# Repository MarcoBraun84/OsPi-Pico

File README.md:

Hier sind alle Projektdatein zum Projekt "OsPi Pico" aus Embedded Systems I vom WS23/24 zu finden.\
Teils wird in "final" und "V1" unterschieden, final bedeutet den Stand am Ende des Projektes, V1 bezieht sich auf die physisch existierenden Platinen.
Sollte an diesen etwas gesucht/geändert werden, kann man sich auzf diese Datein beziehen. Jegliche Verbesserungen oder Weiterentwicklungen sollten aber an den "final" Datein getätigt werden. \

Das Projekt wurde mit Fusion 360 druchgeführt, daher sind viele der umfangreicheren Datein zur Platine nur damit zu öffnen.

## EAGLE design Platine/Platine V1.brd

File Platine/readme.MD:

Die Platinen wurden bei [JLCPCB](https://jlcpcb.com/) gefertigt, ein passender Design-Regelsatz für Fusion 360 kann [hier](https://github.com/oxullo/jlcpcb-eagle) gefunden werden.

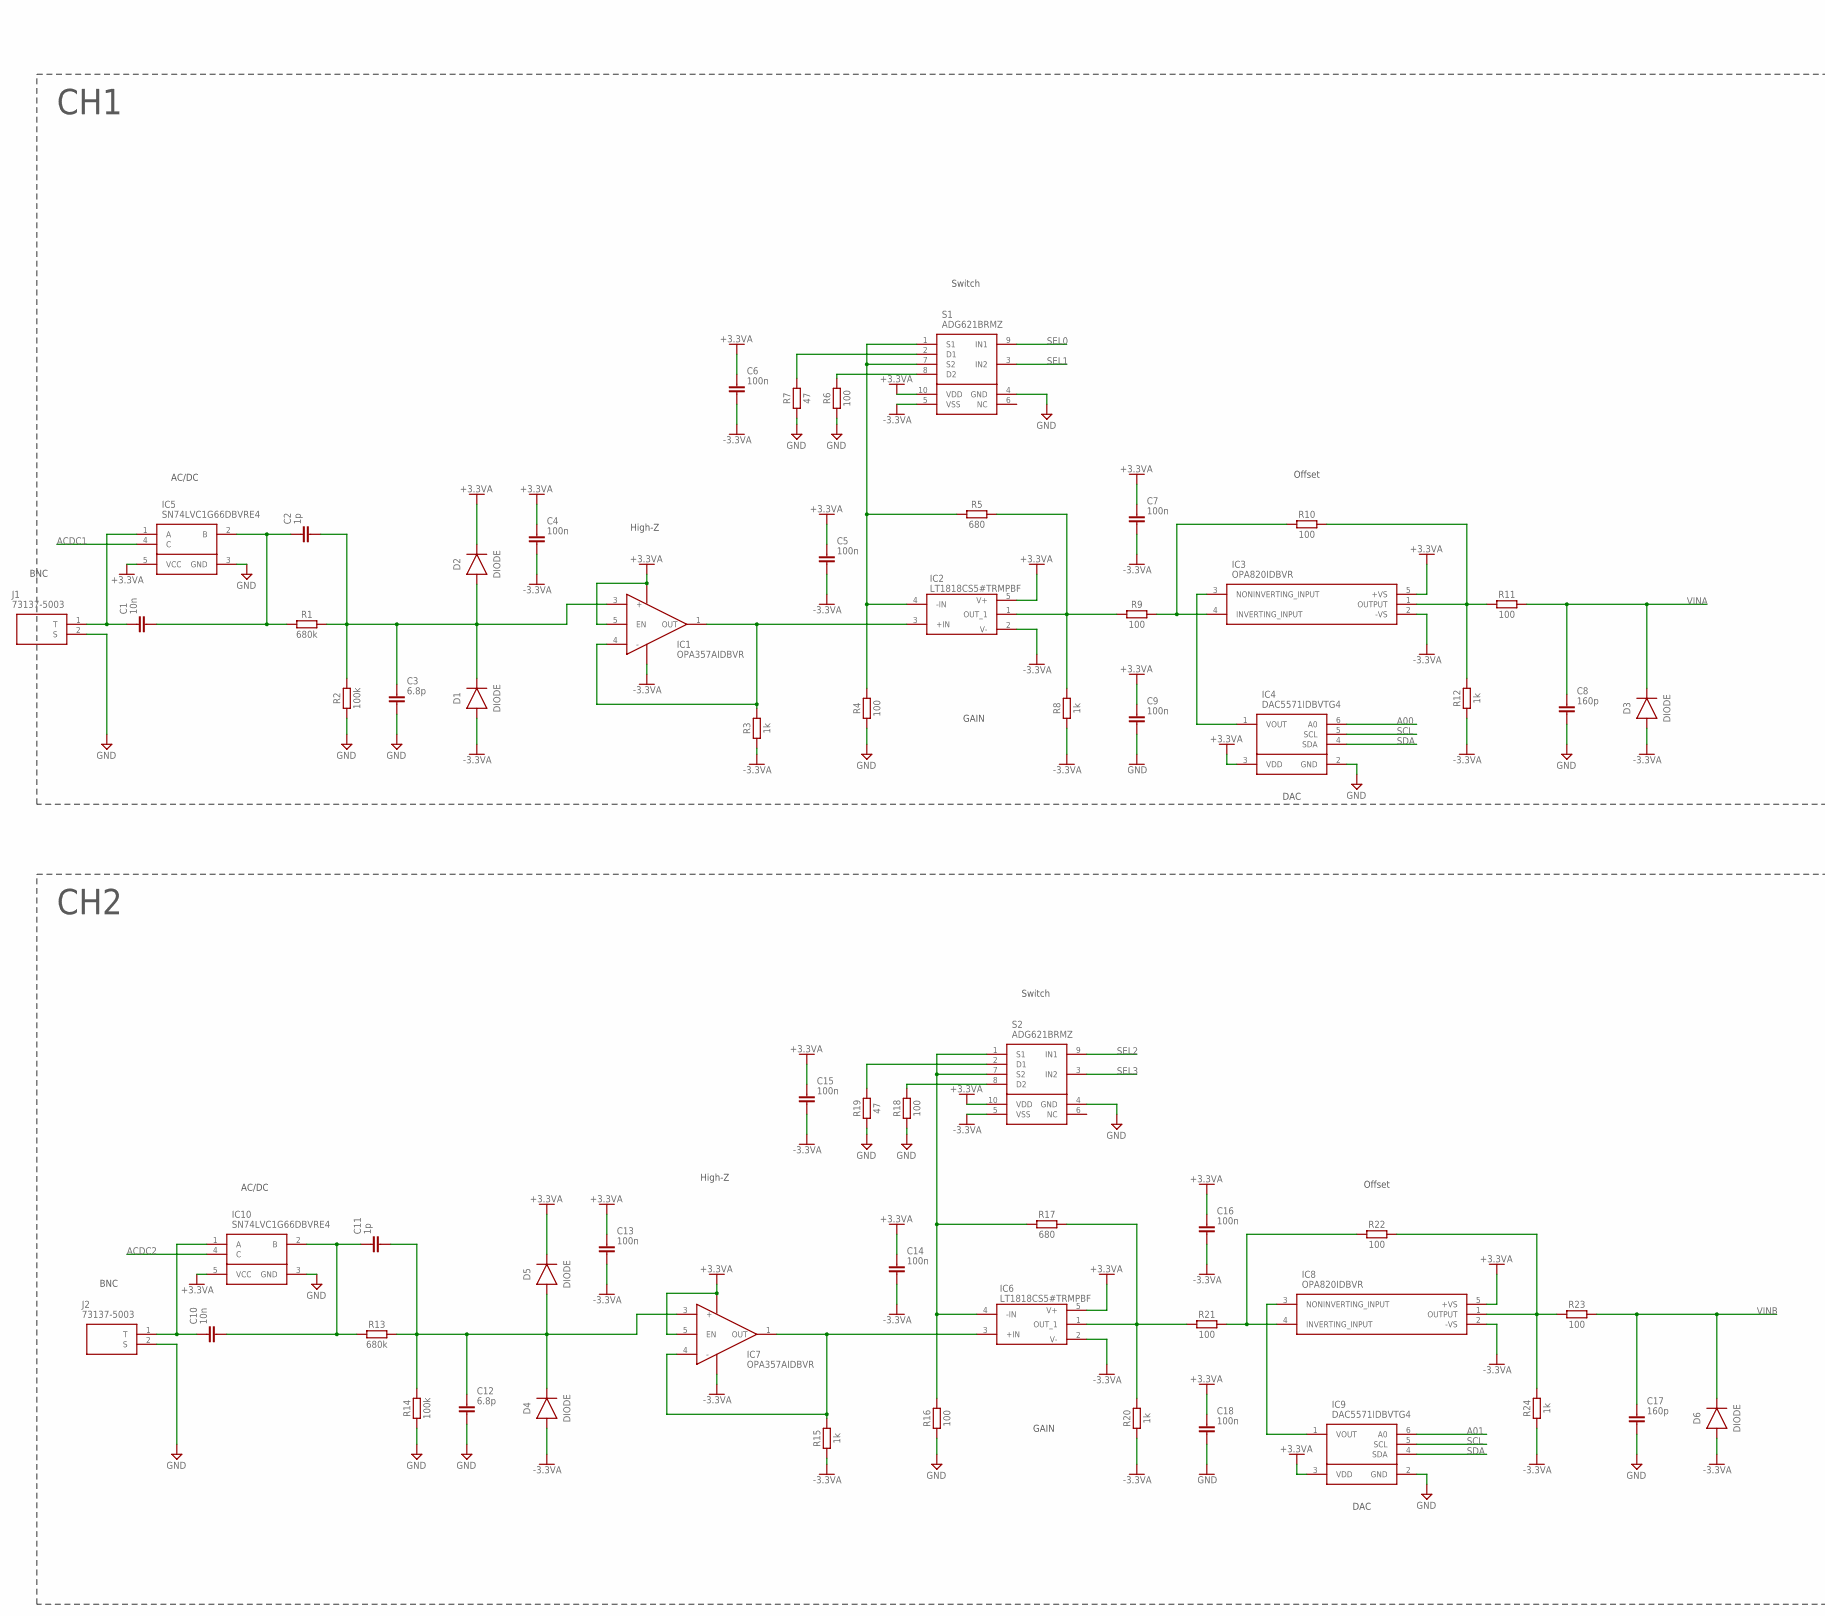
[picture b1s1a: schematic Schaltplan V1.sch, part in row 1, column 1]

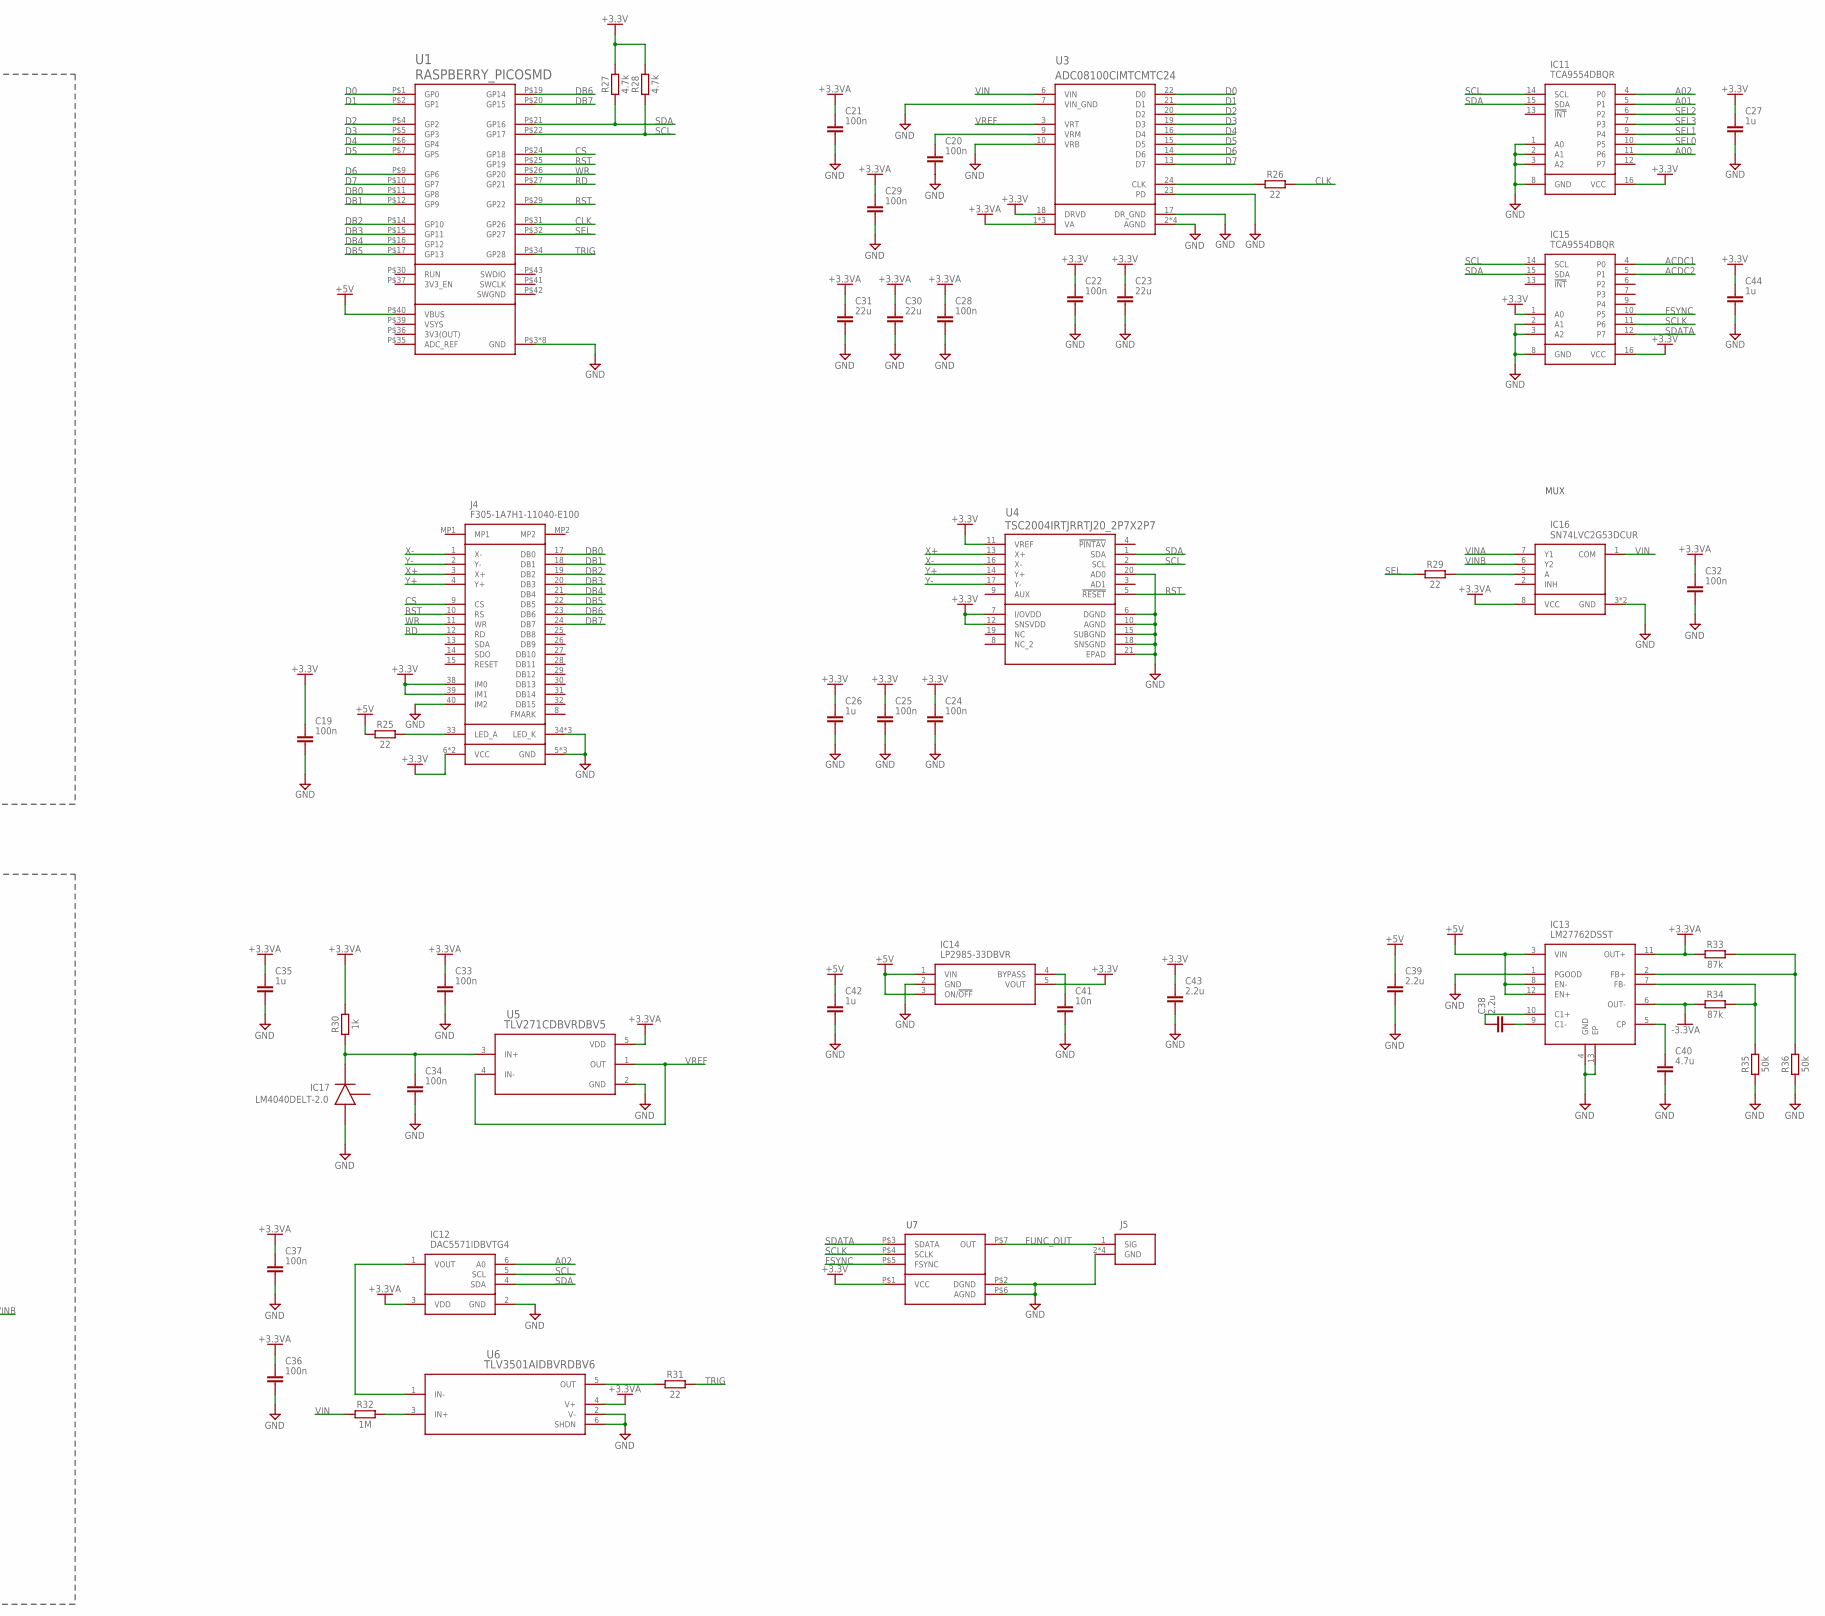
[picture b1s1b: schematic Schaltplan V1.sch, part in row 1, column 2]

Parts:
C1, C10, C41: 10n; CAPC2012X110
C2, C11: 1p; CAPC2012X110
C3, C12: 6.8p; CAPC2012X110
C4, C5, C6, C7, C9, C13, C14, C15, C16, C18, C19, C20, C21, C22, C24, C25, C28, C29, C32, C33, C34, C36, C37: 100n; CAPC2012X110
C8, C17: 160p; CAPC2012X110
C23, C30, C31: 22u; CAPC2012X110
C26, C27, C35, C42, C44: 1u; CAPC2012X110
C38, C39, C43: 2.2u; CAPC2012X110
C40: 4.7u; CAPC2012X110
D1, D2, D3, D4, D5, D6: DIODE; SODFL2513X70
IC1, IC7: OPA357AIDBVR; SOT95P280X145-6N
IC2, IC6: LT1818CS5#TRMPBF; SOT95P280X100-5N
IC3, IC8: OPA820IDBVR; SOT95P280X145-5N
IC4, IC9, IC12: DAC5571IDBVTG4; SOT95P280X145-6N
IC5, IC10: SN74LVC1G66DBVRE4; SOT95P280X145-5N
IC11, IC15: TCA9554DBQR; SOP64P600X175-16N
IC13: LM27762DSST; SON50P200X300X80-13N
IC14: LP2985-33DBVR; SOT95P280X145-5N
IC16: SN74LVC2G53DCUR; SOP50P310X90-8N
IC17: LM4040DELT-2.0; SOT65P210X110-3N
J1, J2: 73137-5003; 731375003
J4: F305-1A7H1-11040-E100; F3051A7H111040E100
J5: PCB.SMAFRA.HT; PCBSMAFRAHT
R1, R13: 680k; RESC2012X65
R2, R14: 100k; RESC2012X65
R3, R8, R12, R15, R20, R24, R30: 1k; RESC2012X65
R4, R6, R9, R10, R11, R16, R18, R21, R22, R23: 100; RESC2012X65
R5, R17: 680; RESC2012X65
R7, R19: 47; RESC2012X65
R25, R26, R29, R31: 22; RESC2012X65
R27, R28: 4.7k; RESC2012X65
R32: 1M; RESC2012X65
R33, R34: 87k; RESC2012X65
R35, R36: 50k; RESC2012X65
S1, S2: ADG621BRMZ; SOP50P490X110-10N
U1: RASPBERRY_PICOSMD; PICO-PKG-SMD
U3: ADC08100CIMTCMTC24; MTC24
U4: TSC2004IRTJRRTJ20_2P7X2P7; RTJ20_2P7X2P7
U5: TLV271CDBVRDBV5; DBV5
U6: TLV3501AIDBVRDBV6; DBV6
U7: AD9833FUNCGEN

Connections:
3V3(OUT): U1.P$36 (3V3(OUT))
+3.3V: C19.1, C22.1, C23.1, C24.1, C25.1, C26.1, C27.1, C43.1, C44.1, IC11.16 (VCC), IC14.5 (VOUT), IC15.1 (A0), IC15.16 (VCC), J4.6 (VCC), J4.7 (VCC), J4.38 (IM0), J4.39 (IM1), R27.2, R28.2, U3.18 (DRVD), U4.7 (I/OVDD), U4.11 (VREF), U4.12 (SNSVDD), U7.P$1 (VCC)
+3.3VA: C4.1, C5.1, C6.1, C7.1, C9.1, C13.1, C14.1, C15.1, C16.1, C18.1, C21.1, C28.1, C29.1, C30.1, C31.1, C32.1, C33.1, C35.1, C36.1, C37.1, D2.1 (C), D5.1 (C), IC1.5 (EN), IC1.6 (V+), IC2.5 (V+), IC3.5 (+VS), IC4.3 (VDD), IC5.5 (VCC), IC6.5 (V+), IC7.5 (EN), IC7.6 (V+), IC8.5 (+VS), IC9.3 (VDD), IC10.5 (VCC), IC12.3 (VDD), IC13.11 (OUT+), IC16.8 (VCC), R30.2, R33.1, S1.10 (VDD), S2.10 (VDD), U3.1 (VA), U3.4 (VA), U3.12 (VA), U5.5 (VDD), U6.4 (V+)
+3.3VA1: C34.1, IC17.1 (K), R30.1, U5.3 (IN+)
+5V: C39.1, C42.1, IC13.3 (VIN), IC13.8 (EN-), IC13.12 (EN+), IC14.1 (VIN), IC14.3 (ON/!OFF), R25.1, U1.P$40 (VBUS)
-3.3VA: C4.2, C5.2, C6.2, C7.2, C13.2, C14.2, C15.2, C16.2, D1.2 (A), D3.2 (A), D4.2 (A), D6.2 (A), IC1.2 (V-), IC2.2 (V-), IC3.2 (-VS), IC6.2 (V-), IC7.2 (V-), IC8.2 (-VS), IC13.6 (OUT-), R3.1, R8.1, R12.1, R15.1, R20.1, R24.1, R34.1, S1.5 (VSS), S2.5 (VSS)
A00: IC4.6 (A0), IC11.11 (P6)
A01: IC9.6 (A0), IC11.5 (P1)
A02: IC11.4 (P0), IC12.6 (A0)
ACDC1: IC5.4 (C), IC15.4 (P0)
ACDC2: IC10.4 (C), IC15.5 (P1)
CLK: R26.2, U1.P$31 (GP26)
CS: J4.9 (CS), U1.P$24 (GP18)
D0: U1.P$1 (GP0), U3.22 (D0)
D1: U1.P$2 (GP1), U3.21 (D1)
D2: U1.P$4 (GP2), U3.20 (D2)
D3: U1.P$5 (GP3), U3.19 (D3)
D4: U1.P$6 (GP4), U3.16 (D4)
D5: U1.P$7 (GP5), U3.15 (D5)
D6: U1.P$9 (GP6), U3.14 (D6)
D7: U1.P$10 (GP7), U3.13 (D7)
DB0: J4.17 (DB0), U1.P$11 (GP8)
DB1: J4.18 (DB1), U1.P$12 (GP9)
DB2: J4.19 (DB2), U1.P$14 (GP10)
DB3: J4.20 (DB3), U1.P$15 (GP11)
DB4: J4.21 (DB4), U1.P$16 (GP12)
DB5: J4.22 (DB5), U1.P$17 (GP13)
DB6: J4.23 (DB6), U1.P$19 (GP14)
DB7: J4.24 (DB7), U1.P$20 (GP15)
FSYNC: IC15.10 (P5), U7.P$5 (FSYNC)
FUNC_OUT: J5.1 (SIG), U7.P$7 (OUT)
GND: C3.2, C8.2, C9.2, C12.2, C17.2, C18.2, C19.2, C20.2, C21.2, C22.2, C23.2, C24.2, C25.2, C26.2, C27.2, C28.2, C29.2, C30.2, C31.2, C32.2, C33.2, C34.2, C35.2, C36.2, C37.2, C39.2, C40.2, C41.2, C42.2, C43.2, C44.2, IC4.2 (GND), IC5.3 (GND), IC9.2 (GND), IC10.3 (GND), IC11.1 (A0), IC11.2 (A1), IC11.3 (A2), IC11.8 (GND), IC12.2 (GND), IC13.1 (PGOOD), IC13.4 (GND), IC13.13 (EP), IC14.2 (GND), IC15.2 (A1), IC15.3 (A2), IC15.8 (GND), IC16.3 (GND), IC16.4 (GND), IC17.2 (A), J1.2 (S), J2.2 (S), J4.5 (GND), J4.16 (GND), J4.34 (LED_K), J4.35 (LED_K), J4.36 (LED_K), J4.37 (GND), J4.40 (IM2), J5.2 (GND), J5.3 (GND), J5.4 (GND), J5.5 (GND), R2.1, R4.1, R6.1, R7.1, R14.1, R16.1, R18.1, R19.1, R35.1, R36.1, S1.4 (GND), S2.4 (GND), U1.P$3 (GND), U1.P$8 (GND), U1.P$13 (GND), U1.P$18 (GND), U1.P$23 (GND), U1.P$28 (GND), U1.P$33 (GND), U1.P$38 (GND), U3.2 (AGND), U3.5 (AGND), U3.7 (VIN_GND), U3.8 (AGND), U3.10 (VRB), U3.11 (AGND), U3.17 (DR_GND), U3.23 (PD), U4.6 (DGND), U4.10 (AGND), U4.15 (SUBGND), U4.18 (SNSGND), U4.20 (AD0), U4.21 (EPAD), U5.2 (GND), U6.2 (V-), U6.6 (SHDN), U7.P$2 (DGND), U7.P$6 (AGND)
unnamed: C1.1, IC5.1 (A), J1.1 (T)
unnamed: C1.2, C2.1, IC5.2 (B), R1.1
unnamed: C2.2, C3.1, D1.1 (C), D2.2 (A), IC1.3 (+), R1.2, R2.2
unnamed: R7.2, S1.2 (D1)
unnamed: IC2.4 (-IN), R4.2, R5.1, S1.1 (S1), S1.7 (S2)
unnamed: IC2.1 (OUT_1), R5.2, R8.2, R9.1
unnamed: IC1.1 (OUT), IC1.4 (-), IC2.3 (+IN), R3.2
unnamed: R6.2, S1.8 (D2)
unnamed: IC3.4 (INVERTING_INPUT), R9.2, R10.1
unnamed: IC3.1 (OUTPUT), R10.2, R11.1, R12.2
unnamed: IC3.3 (NONINVERTING_INPUT), IC4.1 (VOUT)
unnamed: C10.1, IC10.1 (A), J2.1 (T)
unnamed: C10.2, C11.1, IC10.2 (B), R13.1
unnamed: C11.2, C12.1, D4.1 (C), D5.2 (A), IC7.3 (+), R13.2, R14.2
unnamed: IC6.4 (-IN), R16.2, R17.1, S2.1 (S1), S2.7 (S2)
unnamed: IC6.1 (OUT_1), R17.2, R20.2, R21.1
unnamed: IC6.3 (+IN), IC7.1 (OUT), IC7.4 (-), R15.2
unnamed: R19.2, S2.2 (D1)
unnamed: R18.2, S2.8 (D2)
unnamed: IC8.4 (INVERTING_INPUT), R21.2, R22.1
unnamed: IC8.1 (OUTPUT), R22.2, R23.1, R24.2
unnamed: IC8.3 (NONINVERTING_INPUT), IC9.1 (VOUT)
unnamed: R31.1, U6.5 (OUT)
unnamed: R32.2, U6.3 (IN+)
unnamed: IC12.1 (VOUT), U6.1 (IN-)
unnamed: C20.1, U3.9 (VRM)
unnamed: J4.33 (LED_A), R25.2
unnamed: C40.1, IC13.5 (CP)
unnamed: IC13.2 (FB+), R33.2, R36.2
unnamed: C41.1, IC14.4 (BYPASS)
unnamed: IC13.7 (FB-), R34.2, R35.2
unnamed: C38.1, IC13.10 (C1+)
unnamed: C38.2, IC13.9 (C1-)
unnamed: IC16.5 (A), R29.2
unnamed: R26.1, U3.24 (CLK)
RD: J4.12 (RD), U1.P$27 (GP21)
SCL: IC4.5 (SCL), IC9.5 (SCL), IC11.14 (SCL), IC12.5 (SCL), IC15.14 (SCL), R28.1, U1.P$22 (GP17), U4.2 (SCL)
SCLK: IC15.11 (P6), U7.P$4 (SCLK)
SDA: IC4.4 (SDA), IC9.4 (SDA), IC11.15 (SDA), IC12.4 (SDA), IC15.15 (SDA), R27.1, U1.P$21 (GP16), U4.1 (SDA)
SDATA: IC15.12 (P7), U7.P$3 (SDATA)
SEL: R29.1, U1.P$32 (GP27)
SEL0: IC11.10 (P5), S1.9 (IN1)
SEL1: IC11.9 (P4), S1.3 (IN2)
SEL2: IC11.6 (P2), S2.9 (IN1)
SEL3: IC11.7 (P3), S2.3 (IN2)
SWGND: U1.P$42 (SWGND)
TRIG: R31.2, U1.P$34 (GP28)
VIN: IC16.1 (COM), R32.1, U3.6 (VIN)
VINA: C8.1, D3.1 (C), IC16.7 (Y1), R11.2
VINB: C17.1, D6.1 (C), IC16.6 (Y2), R23.2
VREF: U3.3 (VRT), U5.1 (OUT), U5.4 (IN-)
VSYS: U1.P$39 (VSYS)
WR: J4.11 (WR), U1.P$26 (GP20)
X+: J4.3 (X+), U4.13 (X+)
X-: J4.1 (X-), U4.16 (X-)
Y+: J4.4 (Y+), U4.14 (Y+)
Y-: J4.2 (Y-), U4.17 (Y-)

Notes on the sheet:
CH1
BNC
AC/DC
High-Z
Switch
GAIN
Offset
DAC
CH2
MUX

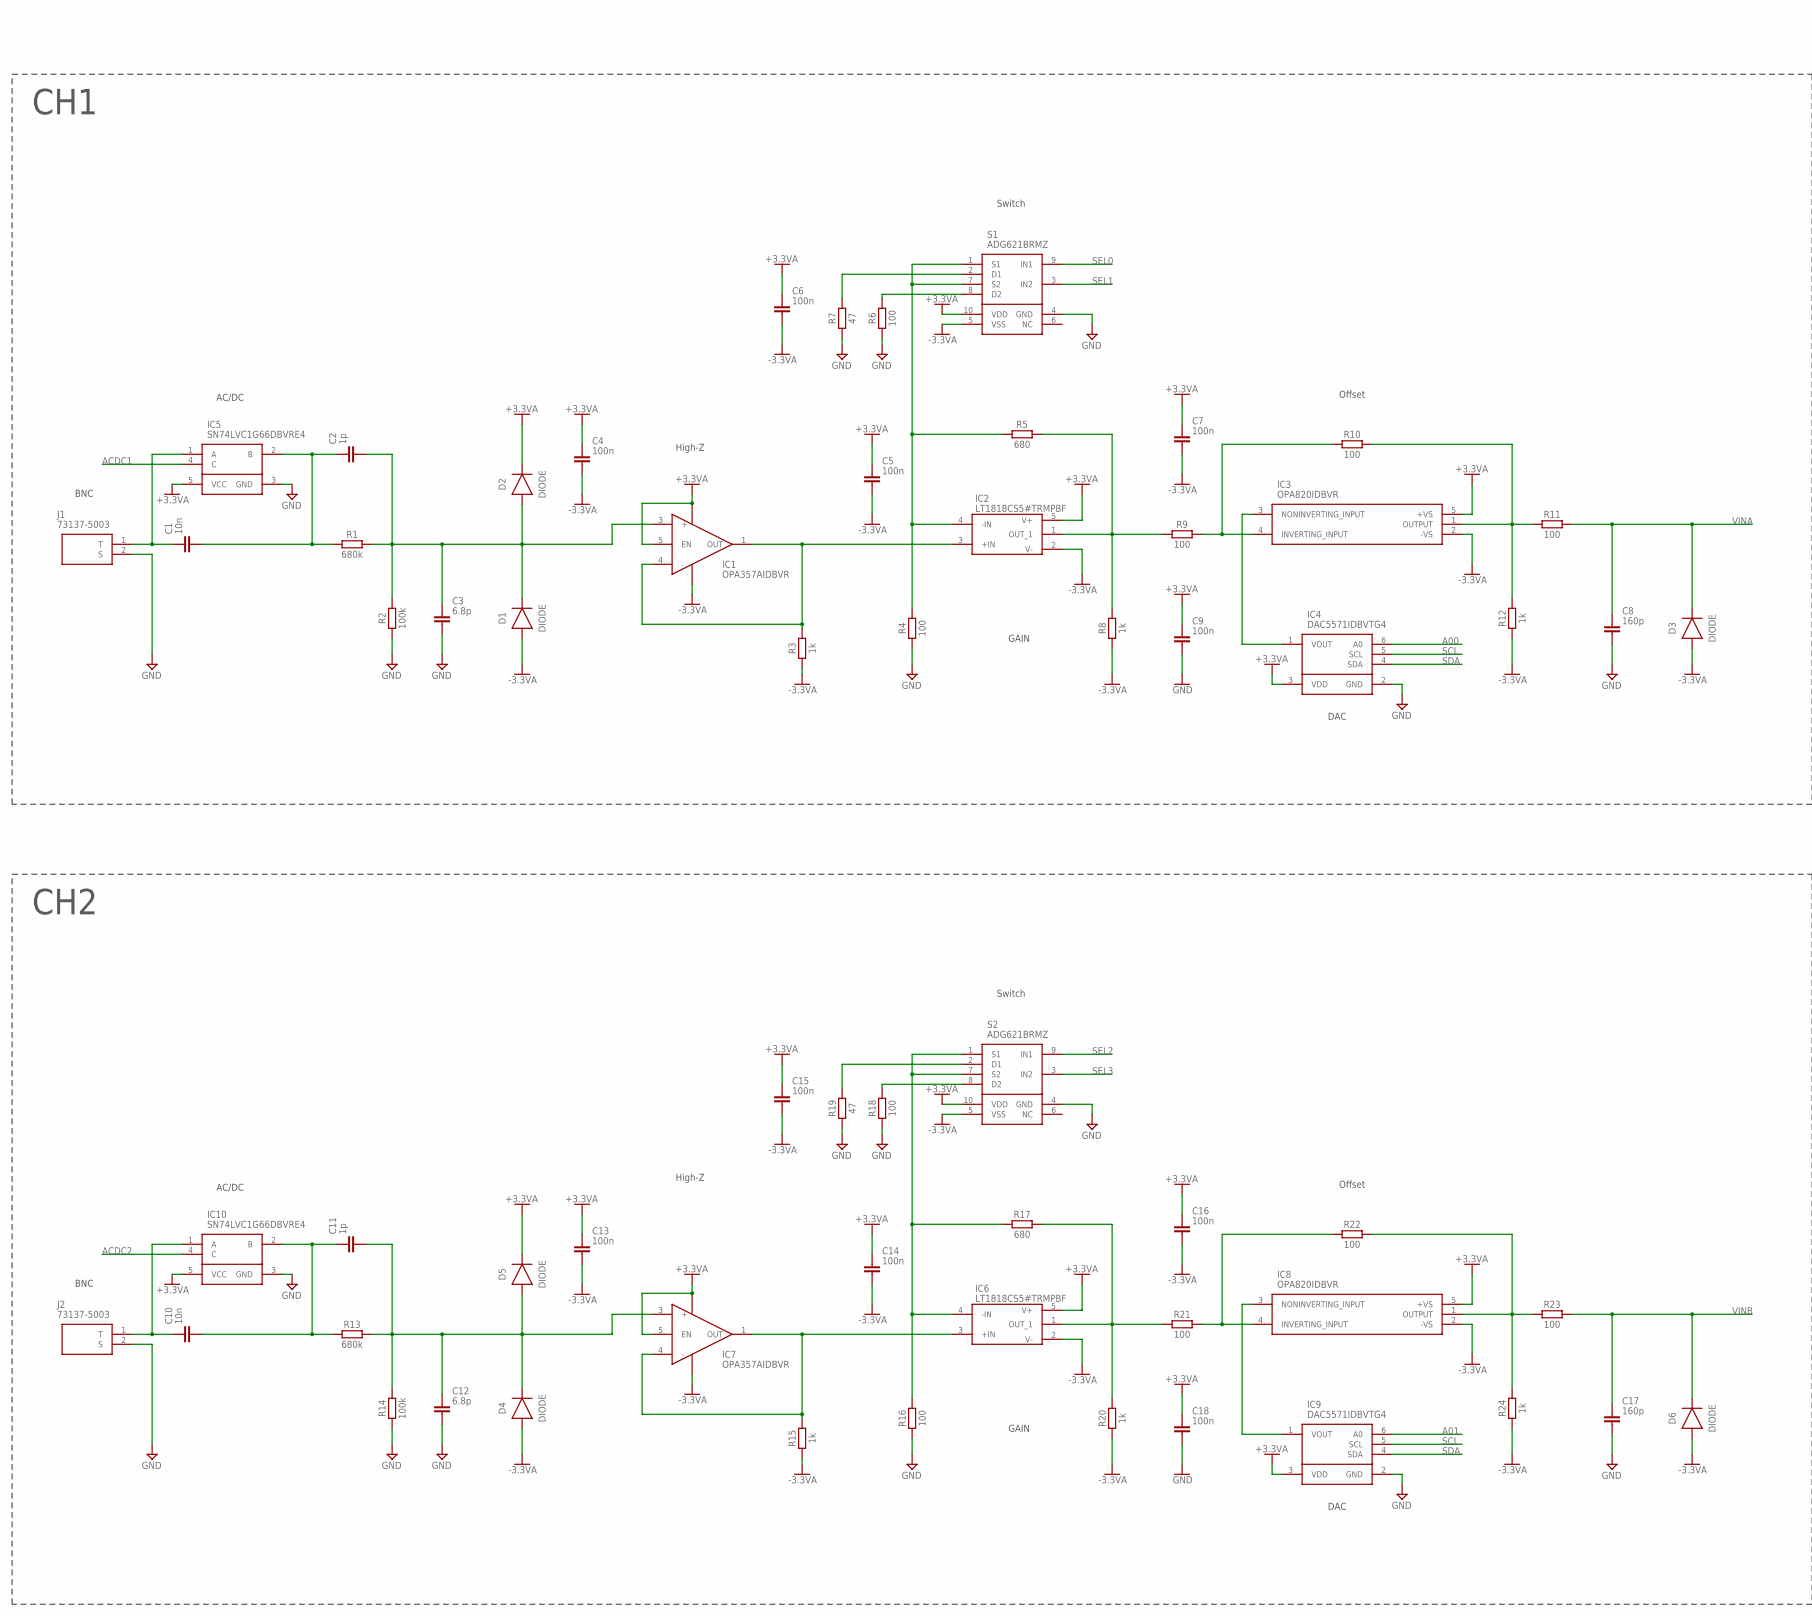
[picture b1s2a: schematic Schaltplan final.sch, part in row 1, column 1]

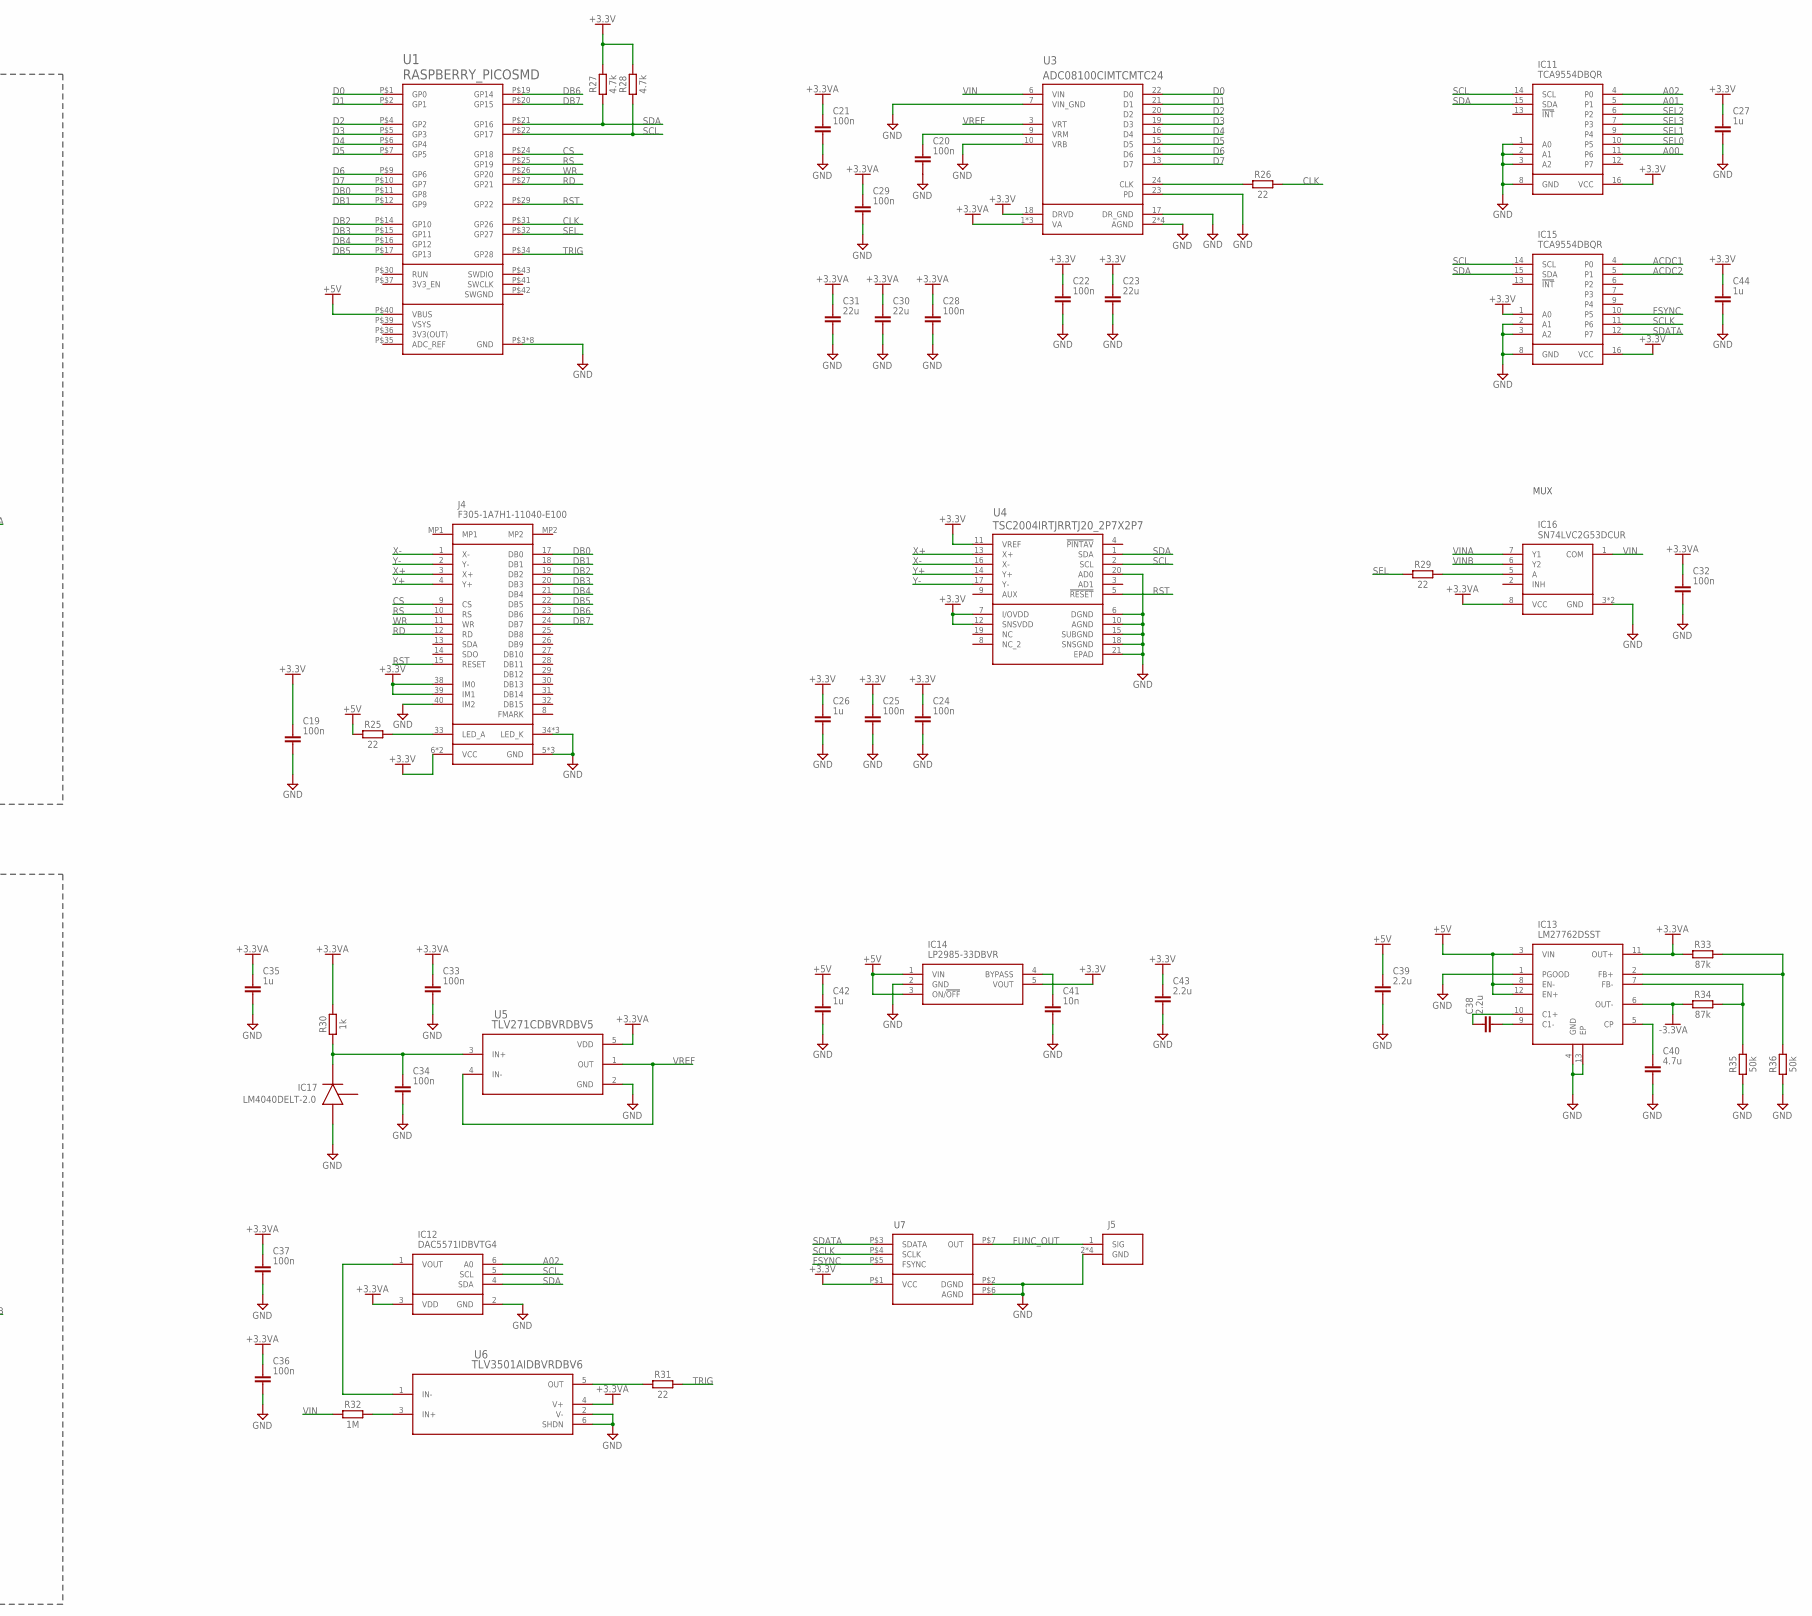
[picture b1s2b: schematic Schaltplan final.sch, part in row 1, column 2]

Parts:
C1, C10, C41: 10n; CAPC2012X110
C2, C11: 1p; CAPC2012X110
C3, C12: 6.8p; CAPC2012X110
C4, C5, C6, C7, C9, C13, C14, C15, C16, C18, C19, C20, C21, C22, C24, C25, C28, C29, C32, C33, C34, C36, C37: 100n; CAPC2012X110
C8, C17: 160p; CAPC2012X110
C23, C30, C31: 22u; CAPC2012X110
C26, C27, C35, C42, C44: 1u; CAPC2012X110
C38, C39, C43: 2.2u; CAPC2012X110
C40: 4.7u; CAPC2012X110
D1, D2, D3, D4, D5, D6: DIODE; SODFL2513X70
IC1, IC7: OPA357AIDBVR; SOT95P280X145-6N
IC2, IC6: LT1818CS5#TRMPBF; SOT95P280X100-5N
IC3, IC8: OPA820IDBVR; SOT95P280X145-5N
IC4, IC9, IC12: DAC5571IDBVTG4; SOT95P280X145-6N
IC5, IC10: SN74LVC1G66DBVRE4; SOT95P280X145-5N
IC11, IC15: TCA9554DBQR; SOP64P600X175-16N
IC13: LM27762DSST; SON50P200X300X80-13N
IC14: LP2985-33DBVR; SOT95P280X145-5N
IC16: SN74LVC2G53DCUR; SOP50P310X90-8N
IC17: LM4040DELT-2.0; SOT65P210X110-3N
J1, J2: 73137-5003; 731375003
J4: F305-1A7H1-11040-E100; F3051A7H111040E100
J5: PCB.SMAFRA.HT; PCBSMAFRAHT
R1, R13: 680k; RESC2012X65
R2, R14: 100k; RESC2012X65
R3, R8, R12, R15, R20, R24, R30: 1k; RESC2012X65
R4, R6, R9, R10, R11, R16, R18, R21, R22, R23: 100; RESC2012X65
R5, R17: 680; RESC2012X65
R7, R19: 47; RESC2012X65
R25, R26, R29, R31: 22; RESC2012X65
R27, R28: 4.7k; RESC2012X65
R32: 1M; RESC2012X65
R33, R34: 87k; RESC2012X65
R35, R36: 50k; RESC2012X65
S1, S2: ADG621BRMZ; SOP50P490X110-10N
U1: RASPBERRY_PICOSMD; PICO-PKG-SMD
U3: ADC08100CIMTCMTC24; MTC24
U4: TSC2004IRTJRRTJ20_2P7X2P7; RTJ20_2P7X2P7
U5: TLV271CDBVRDBV5; DBV5
U6: TLV3501AIDBVRDBV6; DBV6
U7: AD9833FUNCGEN

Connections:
3V3(OUT): U1.P$36 (3V3(OUT))
+3.3V: C19.1, C22.1, C23.1, C24.1, C25.1, C26.1, C27.1, C43.1, C44.1, IC11.16 (VCC), IC14.5 (VOUT), IC15.1 (A0), IC15.16 (VCC), J4.6 (VCC), J4.7 (VCC), J4.38 (IM0), J4.39 (IM1), R27.2, R28.2, U3.18 (DRVD), U4.7 (I/OVDD), U4.11 (VREF), U4.12 (SNSVDD), U7.P$1 (VCC)
+3.3VA: C4.1, C5.1, C6.1, C7.1, C9.1, C13.1, C14.1, C15.1, C16.1, C18.1, C21.1, C28.1, C29.1, C30.1, C31.1, C32.1, C33.1, C35.1, C36.1, C37.1, D2.1 (C), D5.1 (C), IC1.5 (EN), IC1.6 (V+), IC2.5 (V+), IC3.5 (+VS), IC4.3 (VDD), IC5.5 (VCC), IC6.5 (V+), IC7.5 (EN), IC7.6 (V+), IC8.5 (+VS), IC9.3 (VDD), IC10.5 (VCC), IC12.3 (VDD), IC13.11 (OUT+), IC16.8 (VCC), R30.2, R33.1, S1.10 (VDD), S2.10 (VDD), U3.1 (VA), U3.4 (VA), U3.12 (VA), U5.5 (VDD), U6.4 (V+)
+3.3VA1: C34.1, IC17.1 (K), R30.1, U5.3 (IN+)
+5V: C39.1, C42.1, IC13.3 (VIN), IC13.8 (EN-), IC13.12 (EN+), IC14.1 (VIN), IC14.3 (ON/!OFF), R25.1, U1.P$40 (VBUS)
-3.3VA: C4.2, C5.2, C6.2, C7.2, C13.2, C14.2, C15.2, C16.2, D1.2 (A), D3.2 (A), D4.2 (A), D6.2 (A), IC1.2 (V-), IC2.2 (V-), IC3.2 (-VS), IC6.2 (V-), IC7.2 (V-), IC8.2 (-VS), IC13.6 (OUT-), R3.1, R8.1, R12.1, R15.1, R20.1, R24.1, R34.1, S1.5 (VSS), S2.5 (VSS)
A00: IC4.6 (A0), IC11.11 (P6)
A01: IC9.6 (A0), IC11.5 (P1)
A02: IC11.4 (P0), IC12.6 (A0)
ACDC1: IC5.4 (C), IC15.4 (P0)
ACDC2: IC10.4 (C), IC15.5 (P1)
CLK: R26.2, U1.P$31 (GP26)
CS: J4.9 (CS), U1.P$24 (GP18)
D0: U1.P$1 (GP0), U3.22 (D0)
D1: U1.P$2 (GP1), U3.21 (D1)
D2: U1.P$4 (GP2), U3.20 (D2)
D3: U1.P$5 (GP3), U3.19 (D3)
D4: U1.P$6 (GP4), U3.16 (D4)
D5: U1.P$7 (GP5), U3.15 (D5)
D6: U1.P$9 (GP6), U3.14 (D6)
D7: U1.P$10 (GP7), U3.13 (D7)
DB0: J4.17 (DB0), U1.P$11 (GP8)
DB1: J4.18 (DB1), U1.P$12 (GP9)
DB2: J4.19 (DB2), U1.P$14 (GP10)
DB3: J4.20 (DB3), U1.P$15 (GP11)
DB4: J4.21 (DB4), U1.P$16 (GP12)
DB5: J4.22 (DB5), U1.P$17 (GP13)
DB6: J4.23 (DB6), U1.P$19 (GP14)
DB7: J4.24 (DB7), U1.P$20 (GP15)
FSYNC: IC15.10 (P5), U7.P$5 (FSYNC)
FUNC_OUT: J5.1 (SIG), U7.P$7 (OUT)
GND: C3.2, C8.2, C9.2, C12.2, C17.2, C18.2, C19.2, C20.2, C21.2, C22.2, C23.2, C24.2, C25.2, C26.2, C27.2, C28.2, C29.2, C30.2, C31.2, C32.2, C33.2, C34.2, C35.2, C36.2, C37.2, C39.2, C40.2, C41.2, C42.2, C43.2, C44.2, IC4.2 (GND), IC5.3 (GND), IC9.2 (GND), IC10.3 (GND), IC11.1 (A0), IC11.2 (A1), IC11.3 (A2), IC11.8 (GND), IC12.2 (GND), IC13.1 (PGOOD), IC13.4 (GND), IC13.13 (EP), IC14.2 (GND), IC15.2 (A1), IC15.3 (A2), IC15.8 (GND), IC16.3 (GND), IC16.4 (GND), IC17.2 (A), J1.2 (S), J2.2 (S), J4.5 (GND), J4.16 (GND), J4.34 (LED_K), J4.35 (LED_K), J4.36 (LED_K), J4.37 (GND), J4.40 (IM2), J5.2 (GND), J5.3 (GND), J5.4 (GND), J5.5 (GND), R2.1, R4.1, R6.1, R7.1, R14.1, R16.1, R18.1, R19.1, R35.1, R36.1, S1.4 (GND), S2.4 (GND), U1.P$3 (GND), U1.P$8 (GND), U1.P$13 (GND), U1.P$18 (GND), U1.P$23 (GND), U1.P$28 (GND), U1.P$33 (GND), U1.P$38 (GND), U3.2 (AGND), U3.5 (AGND), U3.7 (VIN_GND), U3.8 (AGND), U3.10 (VRB), U3.11 (AGND), U3.17 (DR_GND), U3.23 (PD), U4.6 (DGND), U4.10 (AGND), U4.15 (SUBGND), U4.18 (SNSGND), U4.20 (AD0), U4.21 (EPAD), U5.2 (GND), U6.2 (V-), U6.6 (SHDN), U7.P$2 (DGND), U7.P$6 (AGND)
unnamed: C1.1, IC5.1 (A), J1.1 (T)
unnamed: C1.2, C2.1, IC5.2 (B), R1.1
unnamed: C2.2, C3.1, D1.1 (C), D2.2 (A), IC1.3 (+), R1.2, R2.2
unnamed: R7.2, S1.2 (D1)
unnamed: IC2.4 (-IN), R4.2, R5.1, S1.1 (S1), S1.7 (S2)
unnamed: IC2.1 (OUT_1), R5.2, R8.2, R9.1
unnamed: IC1.1 (OUT), IC1.4 (-), IC2.3 (+IN), R3.2
unnamed: R6.2, S1.8 (D2)
unnamed: IC3.4 (INVERTING_INPUT), R9.2, R10.1
unnamed: IC3.1 (OUTPUT), R10.2, R11.1, R12.2
unnamed: IC3.3 (NONINVERTING_INPUT), IC4.1 (VOUT)
unnamed: C10.1, IC10.1 (A), J2.1 (T)
unnamed: C10.2, C11.1, IC10.2 (B), R13.1
unnamed: C11.2, C12.1, D4.1 (C), D5.2 (A), IC7.3 (+), R13.2, R14.2
unnamed: IC6.4 (-IN), R16.2, R17.1, S2.1 (S1), S2.7 (S2)
unnamed: IC6.1 (OUT_1), R17.2, R20.2, R21.1
unnamed: IC6.3 (+IN), IC7.1 (OUT), IC7.4 (-), R15.2
unnamed: R19.2, S2.2 (D1)
unnamed: R18.2, S2.8 (D2)
unnamed: IC8.4 (INVERTING_INPUT), R21.2, R22.1
unnamed: IC8.1 (OUTPUT), R22.2, R23.1, R24.2
unnamed: IC8.3 (NONINVERTING_INPUT), IC9.1 (VOUT)
unnamed: R31.1, U6.5 (OUT)
unnamed: R32.2, U6.3 (IN+)
unnamed: IC12.1 (VOUT), U6.1 (IN-)
unnamed: C20.1, U3.9 (VRM)
unnamed: J4.33 (LED_A), R25.2
unnamed: C40.1, IC13.5 (CP)
unnamed: IC13.2 (FB+), R33.2, R36.2
unnamed: C41.1, IC14.4 (BYPASS)
unnamed: IC13.7 (FB-), R34.2, R35.2
unnamed: C38.1, IC13.10 (C1+)
unnamed: C38.2, IC13.9 (C1-)
unnamed: IC16.5 (A), R29.2
unnamed: R26.1, U3.24 (CLK)
RD: J4.12 (RD), U1.P$27 (GP21)
SCL: IC4.5 (SCL), IC9.5 (SCL), IC11.14 (SCL), IC12.5 (SCL), IC15.14 (SCL), R28.1, U1.P$22 (GP17), U4.2 (SCL)
SCLK: IC15.11 (P6), U7.P$4 (SCLK)
SDA: IC4.4 (SDA), IC9.4 (SDA), IC11.15 (SDA), IC12.4 (SDA), IC15.15 (SDA), R27.1, U1.P$21 (GP16), U4.1 (SDA)
SDATA: IC15.12 (P7), U7.P$3 (SDATA)
SEL: R29.1, U1.P$32 (GP27)
SEL0: IC11.10 (P5), S1.9 (IN1)
SEL1: IC11.9 (P4), S1.3 (IN2)
SEL2: IC11.6 (P2), S2.9 (IN1)
SEL3: IC11.7 (P3), S2.3 (IN2)
SWGND: U1.P$42 (SWGND)
TRIG: R31.2, U1.P$34 (GP28)
VIN: IC16.1 (COM), R32.1, U3.6 (VIN)
VINA: C8.1, D3.1 (C), IC16.7 (Y1), R11.2
VINB: C17.1, D6.1 (C), IC16.6 (Y2), R23.2
VREF: U3.3 (VRT), U5.1 (OUT), U5.4 (IN-)
VSYS: U1.P$39 (VSYS)
WR: J4.11 (WR), U1.P$26 (GP20)
X+: J4.3 (X+), U4.13 (X+)
X-: J4.1 (X-), U4.16 (X-)
Y+: J4.4 (Y+), U4.14 (Y+)
Y-: J4.2 (Y-), U4.17 (Y-)

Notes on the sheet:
CH1
BNC
AC/DC
High-Z
Switch
GAIN
Offset
DAC
CH2
MUX

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
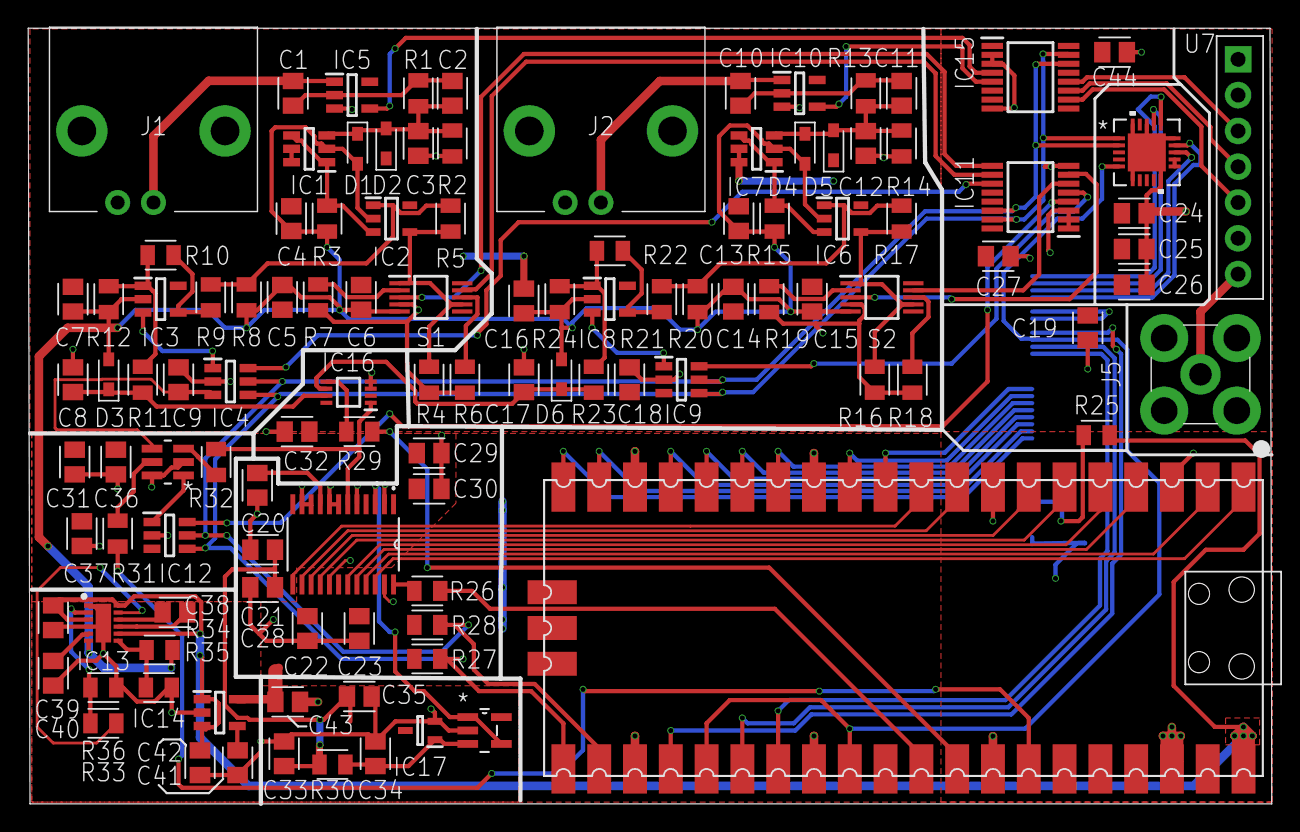
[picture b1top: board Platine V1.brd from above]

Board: 2 copper layers, 88.2 x 55.0 mm, 115 parts (1 on the bottom side), 87 nets.

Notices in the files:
parts and their libraries:
COPYRIGHT: Copyright (C) 2023 Ultra Librarian. All rights reserved.
